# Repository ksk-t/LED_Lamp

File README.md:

# LED Lamp

## Software
### Todo
- User can set profiles via commands
  - Values between 0-255
  - Save on external FRAM via I2C
    - Create custom library to read/write specific profile from/to I2C
  - Smooth transition between profiles
  - Load default profiles if no profiles in FRAM 
- Sleep timer. Slowly dim lights for set amount of time 
- Morning light. Slowly brighten lights in the morning 
- Auto brightness

## Hardware
### Immediate
1. Switching MOSFETS
2. All pin passthrough
3. 3 physical buttons  
    - Power
    - Cycle through profiles (left)
    - Cycle through profiles (right)
### Later
1. FRAM
2. Light\Lux sensor?
3. Rotary Encoder with push + 2 physical buttons
4. Real Time Clock and Calender (RTCC)  
    - Requires 32KHz crystal
### Eagle Guides
- [Schematic](https://learn.sparkfun.com/tutorials/using-eagle-schematic/all)
- [Board Layout](https://learn.sparkfun.com/tutorials/using-eagle-board-layout/all)
### uC32 Reference Eagle Project
[Download Link](https://reference.digilentinc.com/_media/reference/microprocessor/uc32/chipkit_uc32_bysa_a.zip)

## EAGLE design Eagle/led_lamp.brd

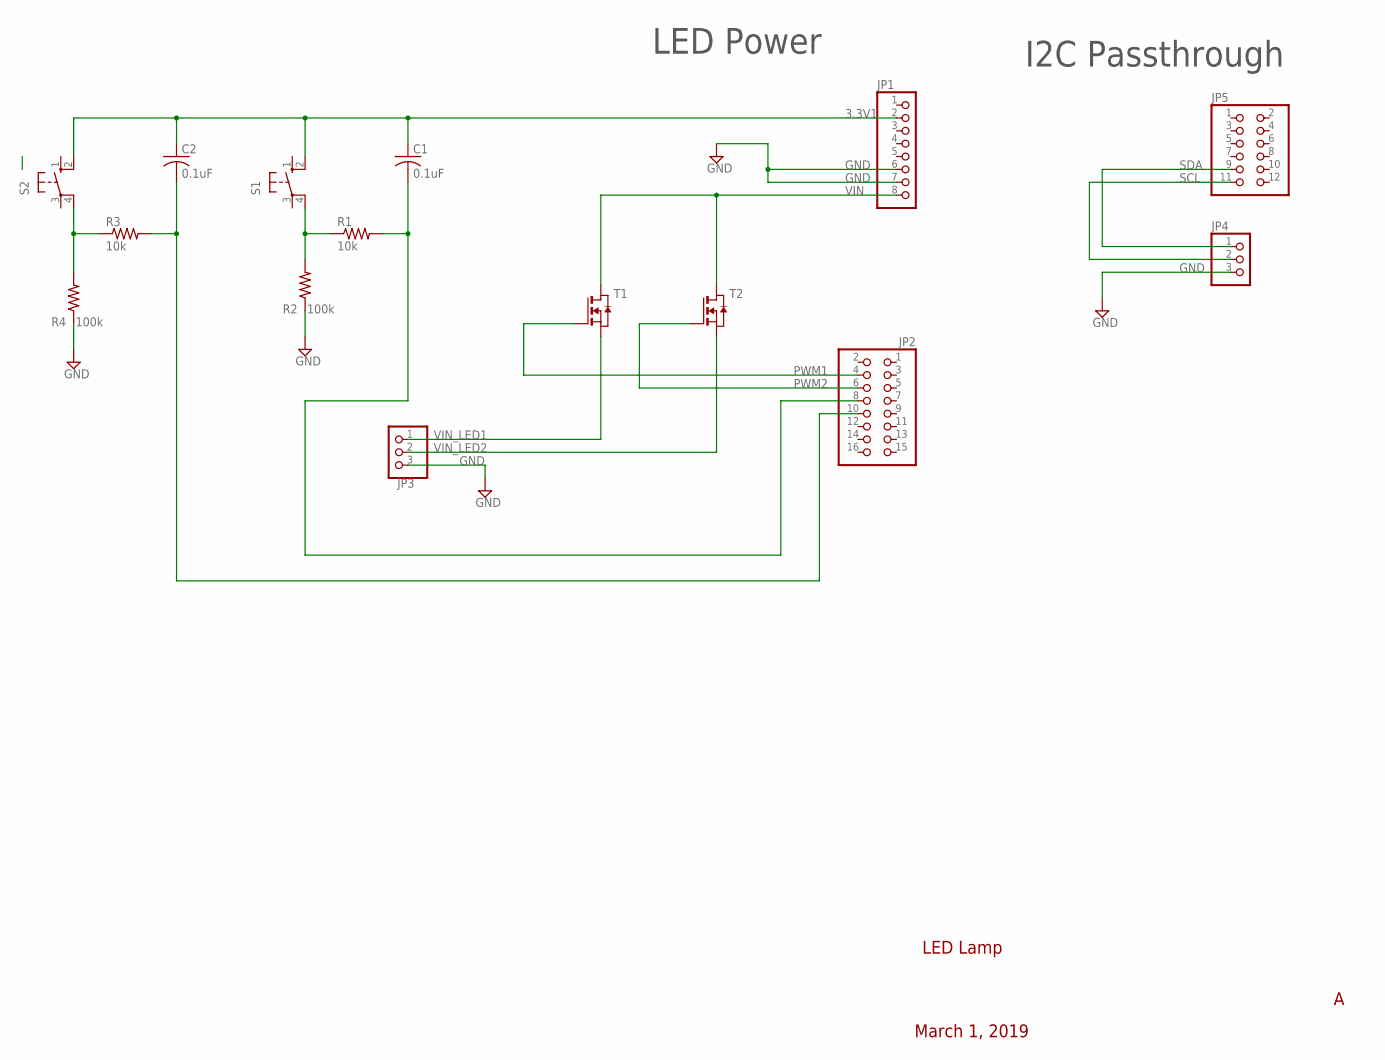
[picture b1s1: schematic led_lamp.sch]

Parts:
C1, C2: 0.1uF; C1206K
JP1: PINHD-1X8; 1X08
JP2: PINHD-2X8; 2X08
JP3, JP4: PINHD-1X3; 1X03
JP5: PINHD-2X6; 2X06
R1, R3: 10k; R1206
R2, R4: 100k; R1206
S1, S2: 10-XX; B3F-10XX
T1, T2: NMOSSOT23; SOT-23

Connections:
3.3V1: C1.1, C2.1, JP1.2, S1.2 (S1), S2.2 (S1)
GND: JP1.6, JP1.7, JP3.3, JP4.3, R2.1, R4.1
unnamed: R1.1, R2.2, S1.4 (P1)
unnamed: C1.2, JP2.8, R1.2
unnamed: R3.1, R4.2, S2.4 (P1)
unnamed: C2.2, JP2.10, R3.2
PWM1: JP2.4, T1.3 (G)
PWM2: JP2.6, T2.3 (G)
SCL: JP4.2, JP5.11
SDA: JP4.1, JP5.9
VIN: JP1.8, T1.1 (D), T2.1 (D)
VIN_LED1: JP3.1, T1.2 (S)
VIN_LED2: JP3.2, T2.2 (S)

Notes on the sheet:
LED Lamp
March 1, 2019
LED Power
I2C Passthrough

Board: 2 copper layers, 15 parts (0 on the bottom side), 13 nets, no tracks yet.

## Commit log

2019-03-02 First eagle draft
2019-03-02 Updated README
    Added link to eagle guides. Updated hardware ideas.
2019-03-02 Update README.md
    Added link to uc32 eagle project to use as reference
2019-03-03 Fixed typo
2019-03-04 Updated arduino project and eagle project
    Eagle:
    - Added push button along with auxiliary componetns
    Arduino Project
    - Added profiles
    - Added serial command to set both LEDs with one command
    - Merged seperate set_led functions into one
2019-03-09 Added pwr button to eagle pcb
2019-03-18 Major update
    -Replace defines with local constants
    -Uses class structure for button and LED control
    -LEDs will now change together in the same loop. Before one LED would change after the other.
    -Remove serial
    -Add power off button
2019-03-20 Update led_lamp_arduino.ino
    -Renamed Led_controller to LedController
    -Replaced Led pointers in LedController to Led objects
